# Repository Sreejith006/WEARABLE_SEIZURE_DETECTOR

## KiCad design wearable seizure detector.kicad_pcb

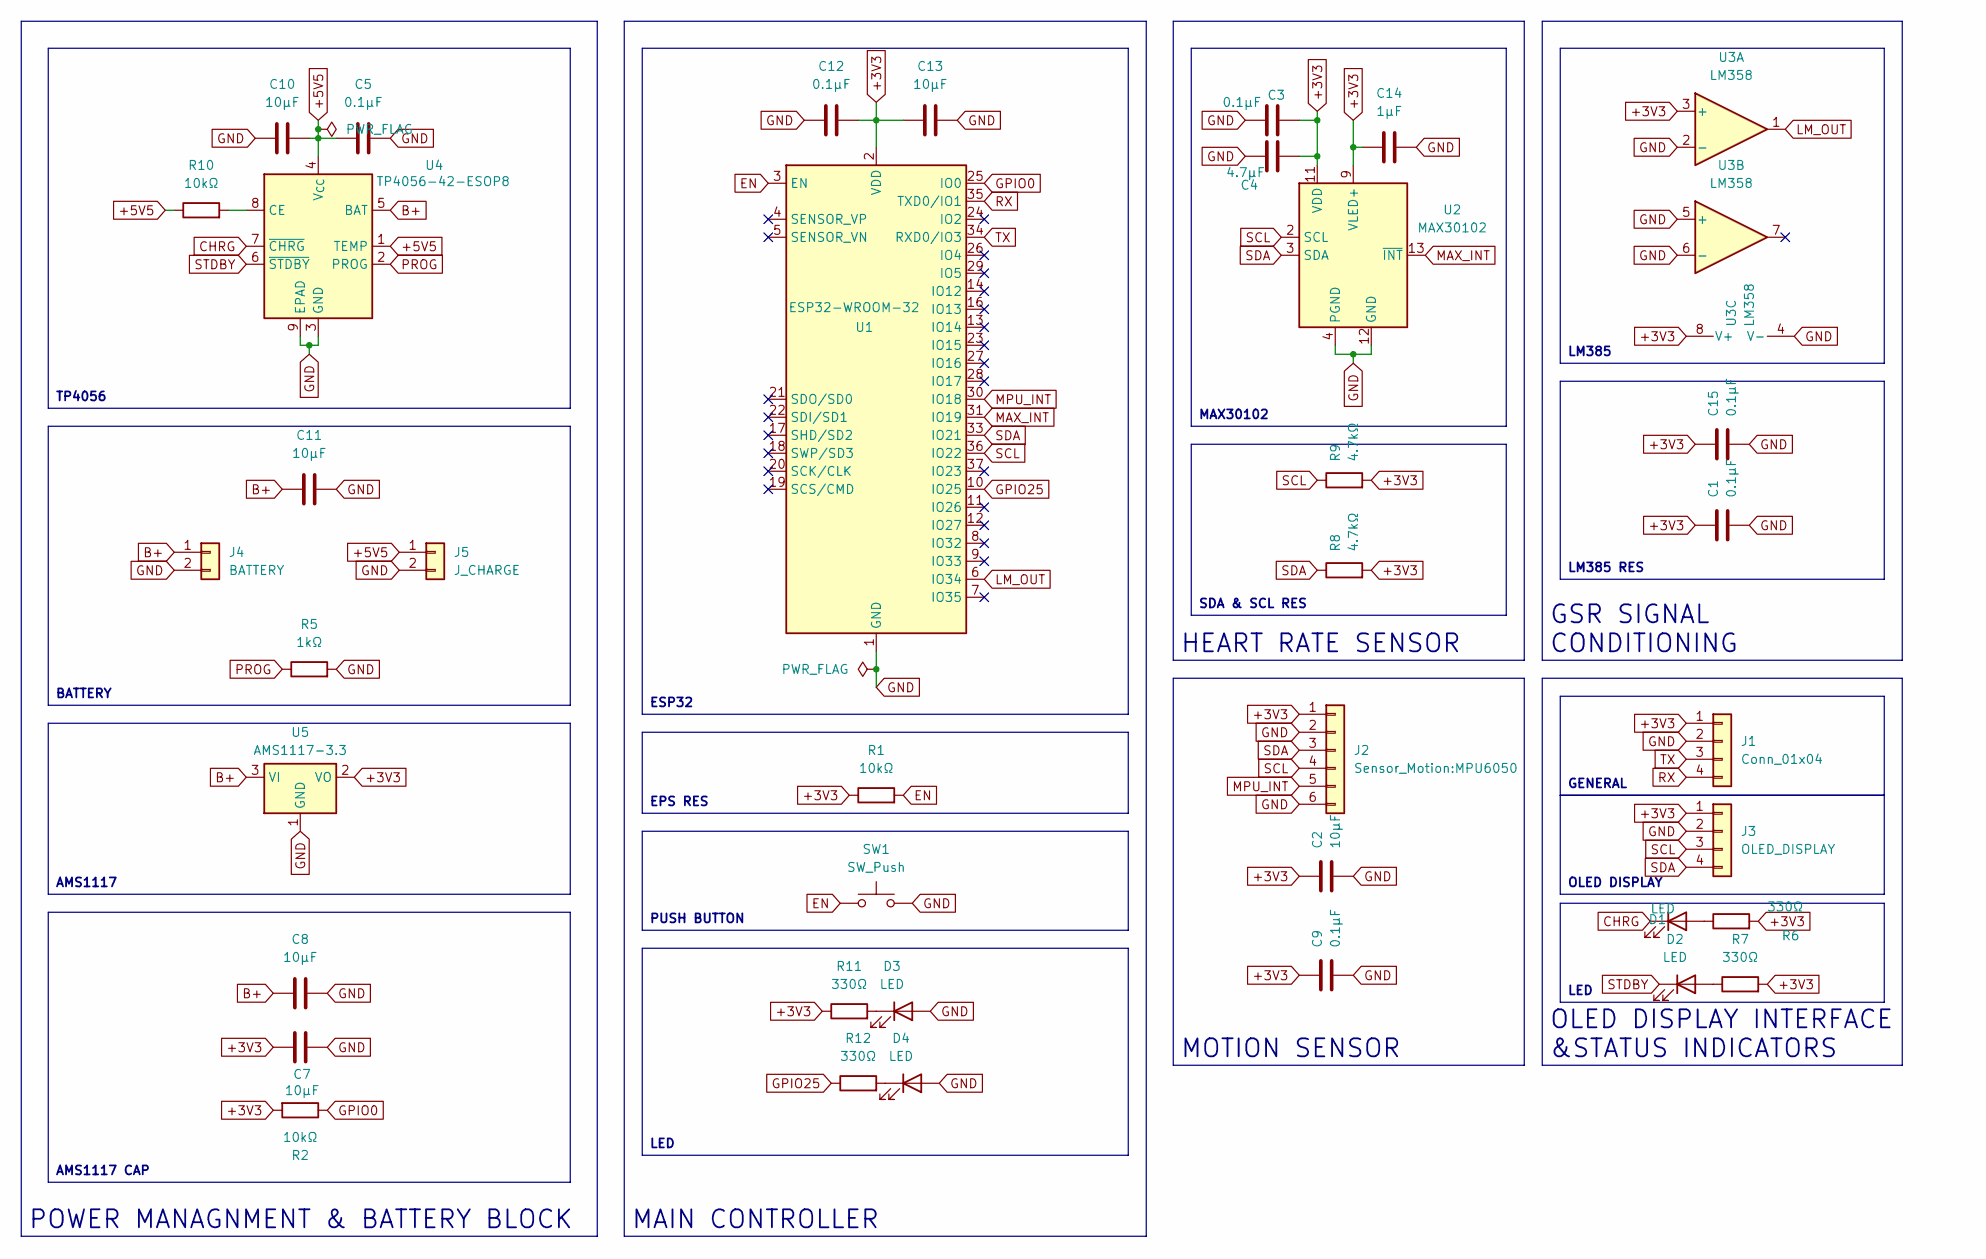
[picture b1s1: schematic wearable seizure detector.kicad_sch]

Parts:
C1, C3, C5, C9, C12, C15: 0.1µF; C_0603_1608Metric
C2, C7, C8, C10, C11, C13: 10µF; C_0805_2012Metric
C4: 4.7µF; C_0805_2012Metric
C14: 1µF; C_0805_2012Metric
D1, D2, D3, D4: LED; LED_0603_1608Metric
J1: Conn_01x04; PinHeader_1x04_P2.54mm_Vertical
J2: Sensor_Motion:MPU6050; PinHeader_1x06_P2.54mm_Vertical
J3: OLED_DISPLAY; PinHeader_1x04_P2.54mm_Vertical
J4: BATTERY; JST_PH_B2B-PH-K_1x02_P2.00mm_Vertical
J5: J_CHARGE; PinHeader_1x02_P2.54mm_Vertical
R1, R2, R10: 10kΩ; R_0603_1608Metric
R5: 1kΩ; R_0603_1608Metric
R6, R7, R11, R12: 330Ω; R_0603_1608Metric
R8, R9: 4.7kΩ; R_0603_1608Metric
SW1: SW_Push; SW_SPST_EVQP0
U1: ESP32-WROOM-32
U2: MAX30102; Maxim_OLGA-14_3.3x5.6mm_P0.8mm
U3: LM358; SOIC-8_3.9x4.9mm_P1.27mm
U4: TP4056-42-ESOP8; SOIC-8-1EP_3.9x4.9mm_P1.27mm_EP2.41x3.3mm_ThermalVias
U5: AMS1117-3.3; SOT-223-3_TabPin2

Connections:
+3V3: C1.1, C2.1, C3.1, C4.1, C7.1, C9.1, C12.2, C13.1, C14.1, C15.1, J1.1, J2.1, J3.1, R1.1, R2.2, R6.2, R7.2, R8.2, R9.2, R11.1, U1.2 (VDD), U2.9 (VLED+), U2.10 (VLED+), U2.11 (VDD), U3.3 (+), U3.8 (V+), U5.2 (VO)
+5V5: C5.1, C10.2, J5.1, R10.1, U4.1 (TEMP), U4.4 (V_{CC})
B+: C8.1, C11.1, J4.1, U4.5 (BAT), U5.3 (VI)
CHRG: D1.1 (K), U4.7 (~CHRG)
EN: R1.2, SW1.1, U1.3 (EN)
GND: C1.2, C2.2, C3.2, C4.2, C5.2, C7.2, C8.2, C9.2, C10.1, C11.2, C12.1, C13.2, C14.2, C15.2, D3.2 (A), D4.2 (A), J1.2, J2.2, J2.6, J3.2, J4.2, J5.2, R5.2, SW1.2, U1.1 (GND), U1.15 (GND), U1.38 (GND), U1.39 (GND), U2.4 (PGND), U2.12 (GND), U3.2 (-), U3.4 (V-), U3.5 (+), U3.6 (-), U4.3 (GND), U4.9 (EPAD), U5.1 (GND)
GPIO0: R2.1, U1.25 (IO0)
GPIO25: R12.1, U1.10 (IO25)
LM_OUT: U1.6 (IO34), U3.1
MAX_INT: U1.31 (IO19), U2.13 (~INT)
MPU_INT: J2.5, U1.30 (IO18)
unnamed: D1.2 (A), R6.1
unnamed: D2.2 (A), R7.1
unnamed: D3.1 (K), R11.2
unnamed: D4.1 (K), R12.2
unnamed: R10.2, U4.8 (CE)
PROG: R5.1, U4.2 (PROG)
RX: J1.4, U1.35 (TXD0/IO1)
SCL: J2.4, J3.3, R9.1, U1.36 (IO22), U2.2 (SCL)
SDA: J2.3, J3.4, R8.1, U1.33 (IO21), U2.3 (SDA)
STDBY: D2.1 (K), U4.6 (~STDBY)
TX: J1.3, U1.34 (RXD0/IO3)

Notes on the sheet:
EPS RES
ESP32
LM385
GENERAL
SDA & SCL RES
LM385 RES
AMS1117
LED
HEART RATE SENSOR
AMS1117 CAP
POWER MANAGNMENT & BATTERY BLOCK
BATTERY
MAX30102
LED
MAIN CONTROLLER
PUSH BUTTON
MOTION SENSOR
GSR SIGNAL CONDITIONING
OLED DISPLAY INTERFACE &STATUS INDICATORS
OLED DISPLAY
TP4056

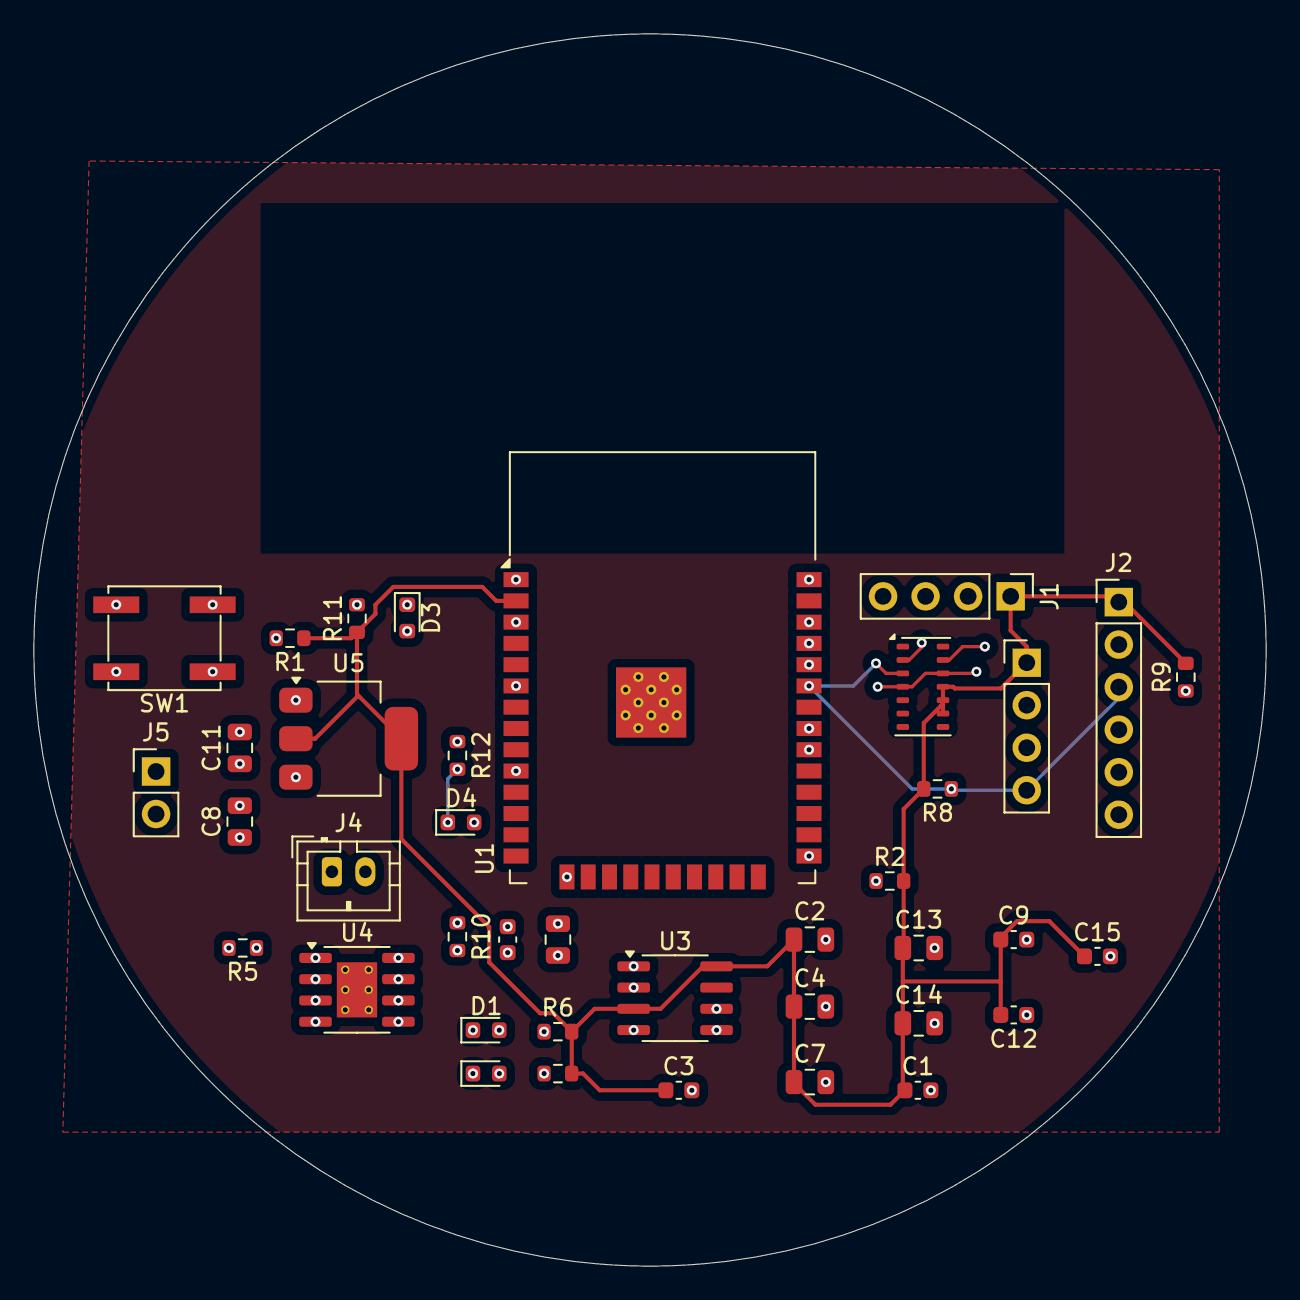
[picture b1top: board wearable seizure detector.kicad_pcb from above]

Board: 16 copper layers, 73.6 x 73.6 mm, 39 parts (0 on the bottom side), 22 nets.

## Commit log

2026-03-13 Add files via upload
    PCB FILES
2026-03-13 Add files via upload
    GERBER FILE
